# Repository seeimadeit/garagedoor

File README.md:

# Garage Door Opener

Project Status: Unstable - in development

 * circuit design - stable
* iphone software - unstable
* arduino software - unstable
* box housing - stable/regular changes

Project located @ 
[https://github.com/seeimadeit/garagedoor](https://github.com/seeimadeit/garagedoor "Github")
and [https://seeimadeit.wordpress.com/](https://seeimadeit.wordpress.com/ "Wordpress")

This hardware device is a simple Arduino based relay controller, it uses the Adafruit BLE nRF8001 [http://www.adafruit.com/products/1697](http://www.adafruit.com/products/1697 "Adafruit website").

Stuff I use to make it

* Hardware
	1. circuitboard Eagle CAD 7.4.0
	2. Housing Cubify Design 2014
* Software
	1. Apple XCode 7.1.x, Swift 2 - iPhone
	2. Arduino 1.6.5
	3. Libraries
		* MD5 - https://github.com/scottmac/arduino
		* BLE - https://github.com/sandeepmistry/arduino-BLEPeripheral

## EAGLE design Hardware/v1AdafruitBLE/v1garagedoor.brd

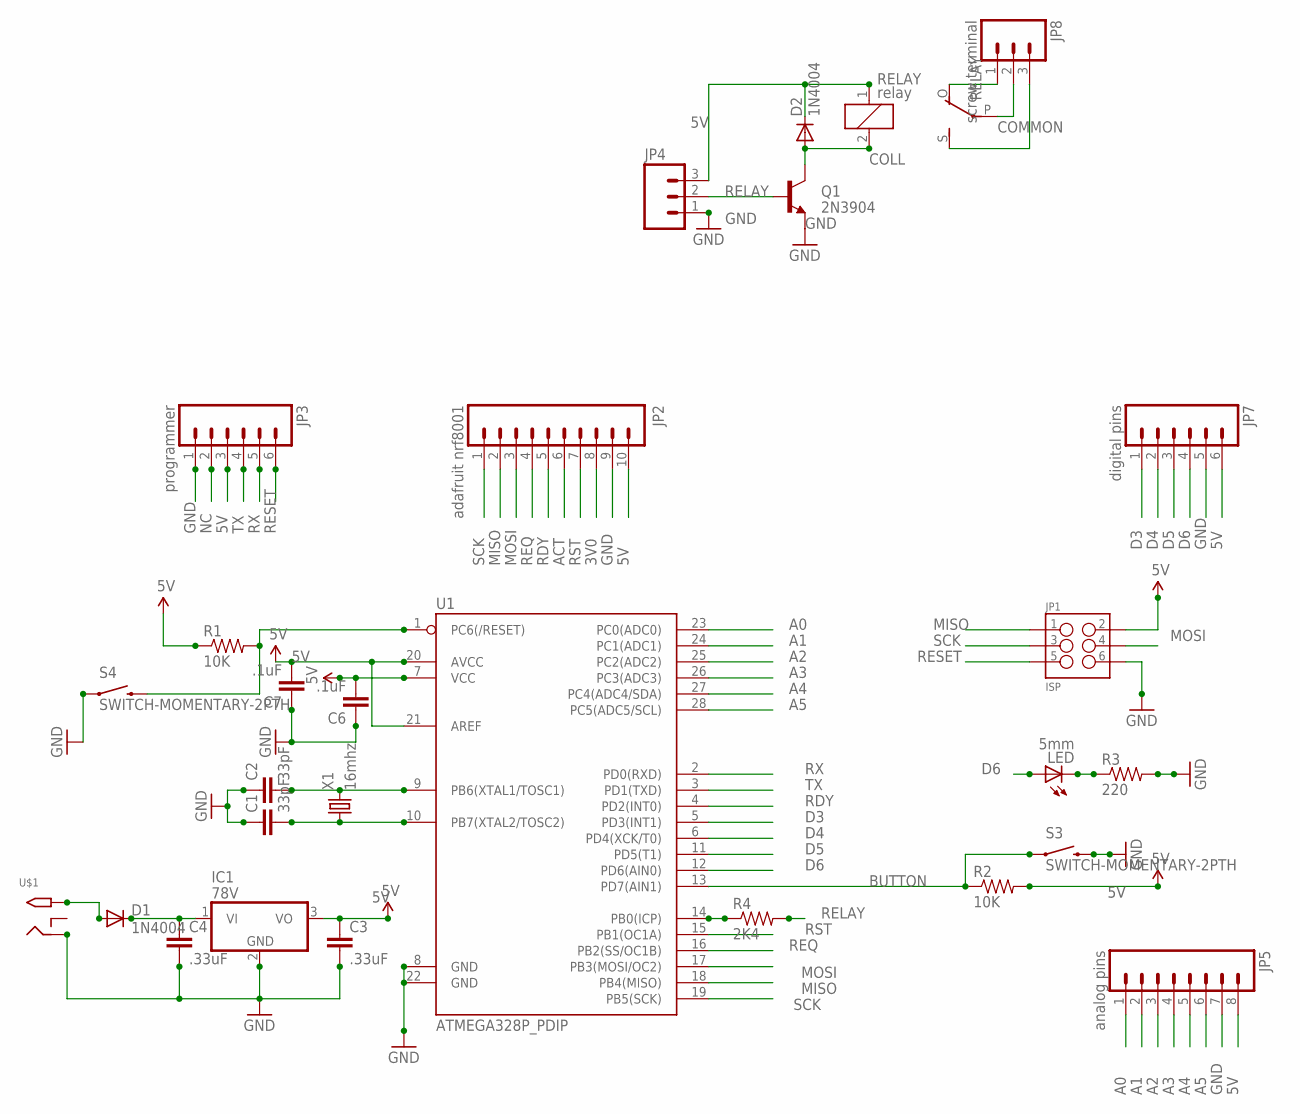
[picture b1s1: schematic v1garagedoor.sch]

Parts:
C1, C2: 33pF; CAP-PTH-5MM; MOUSER 594-S200K25SL0N63L6R
C3, C4: .33uF; CAP-PTH-SMALL-KIT; MOUSER 810-FK18X5R1A334K
C6, C7: .1uF; CAP-PTH-SMALL-KIT; MOUSER 810-FK18X5R1A334K
D1, D2: 1N4004; DO41-10; MOUSER 621-1N4004
IC1: 78V; TO220V; MOUSER 863-MC7805CTG
JP1: ISP; 2X3-NS; MOUSER 571-5-146252-3
JP2: adafruit nrf8001; 1X10; MOUSER 992-10FX1-254MM
JP3: programmer; 1X06_NO_SILK
JP4: M03LOCK; 1X03_LOCK
JP5: analog pins; 1X08
JP7: digital pins; 1X06_NO_SILK
JP8: screw terminal; SCREWTERMINAL-3.5MM-3
LED: 5mm; LED5MM
Q1: 2N3904; TO-92; MOUSER 610-2N3904
R1, R2: 10K; AXIAL-0.3; MOUSER 603-CFR-25JR-5210K
R3: 220; AXIAL-0.3; MOUSER 603-CFR-25JR-52220R
R4: 2K4; AXIAL-0.3; MOUSER 603-CFR-25JR-52-680R
RELAY: relay; ZF112; MOUSER 655-ORWH-SH105D1F000
S3, S4: SWITCH-MOMENTARY-2PTH; TACTILE-PTH; MOUSER 693-1301.9301
U1: ATMEGA328P_PDIP; DIL28-3; MOUSER 556-ATMEGA328P-PU
U$1: 2.1MMJACKTHM; PJ-102A; MOUSER 992-CON-SOCJ-2155
X1: 16mhz; TC38H; MOUSER 520-160-20-46X

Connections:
3V0: JP2.8
5V: C3.1, C6.2, C7.2, D2.C, IC1.3 (VO), JP1.2, JP2.10, JP3.3, JP4.3, JP5.8, JP7.6, R1.P$1 (1), R2.P$2 (2), RELAY.1, U1.7 (VCC), U1.20 (AVCC), U1.21 (AREF)
12V: D1.A, U$1.TIP
A0: JP5.1, U1.23 (PC0(ADC0))
A1: JP5.2, U1.24 (PC1(ADC1))
A2: JP5.3, U1.25 (PC2(ADC2))
A3: JP5.4, U1.26 (PC3(ADC3))
A4: JP5.5, U1.27 (PC4(ADC4/SDA))
A5: JP5.6, U1.28 (PC5(ADC5/SCL))
ACT: JP2.6
BUTTON: R2.P$1 (1), S3.1, U1.13 (PD7(AIN1))
COLL: D2.A, Q1.3 (C), RELAY.2
COMMON: JP8.2, RELAY.P
D3: JP7.1, U1.5 (PD3(INT1))
D4: JP7.2, U1.6 (PD4(XCK/T0))
D5: JP7.3, U1.11 (PD5(T1))
D6: JP7.4, LED.A, U1.12 (PD6(AIN0))
GND: C1.1, C2.1, C3.2, C4.2, C6.1, C7.1, IC1.2 (GND), JP1.6, JP2.9, JP3.1, JP4.1, JP5.7, JP7.5, Q1.1 (E), R3.P$2 (2), S3.3 (2), S4.1, U1.8 (GND), U1.22 (GND), U$1.RING
MISO: JP1.1, JP2.2, U1.18 (PB4(MISO))
MOSI: JP1.4, JP2.3, U1.17 (PB3(MOSI/OC2))
unnamed: C2.2, U1.9 (PB6(XTAL1/TOSC1)), X1.2
unnamed: C1.2, U1.10 (PB7(XTAL2/TOSC2)), X1.1
unnamed: C4.1, D1.C, IC1.1 (VI)
unnamed: LED.K (C), R3.P$1 (1)
unnamed: JP8.1, RELAY.O
unnamed: JP8.3, RELAY.S
unnamed: R4.P$1 (1), U1.14 (PB0(ICP))
NC: JP3.2
RDY: JP2.5, U1.4 (PD2(INT0))
RELAY: JP4.2, Q1.2 (B), R4.P$2 (2)
REQ: JP2.4, U1.16 (PB2(SS/OC1B))
RESET: JP1.5, JP3.6, R1.P$2 (2), S4.3 (2), U1.1 (PC6(/RESET))
RST: JP2.7, U1.15 (PB1(OC1A))
RX: JP3.5, U1.2 (PD0(RXD))
SCK: JP1.3, JP2.1, U1.19 (PB5(SCK))
TX: JP3.4, U1.3 (PD1(TXD))

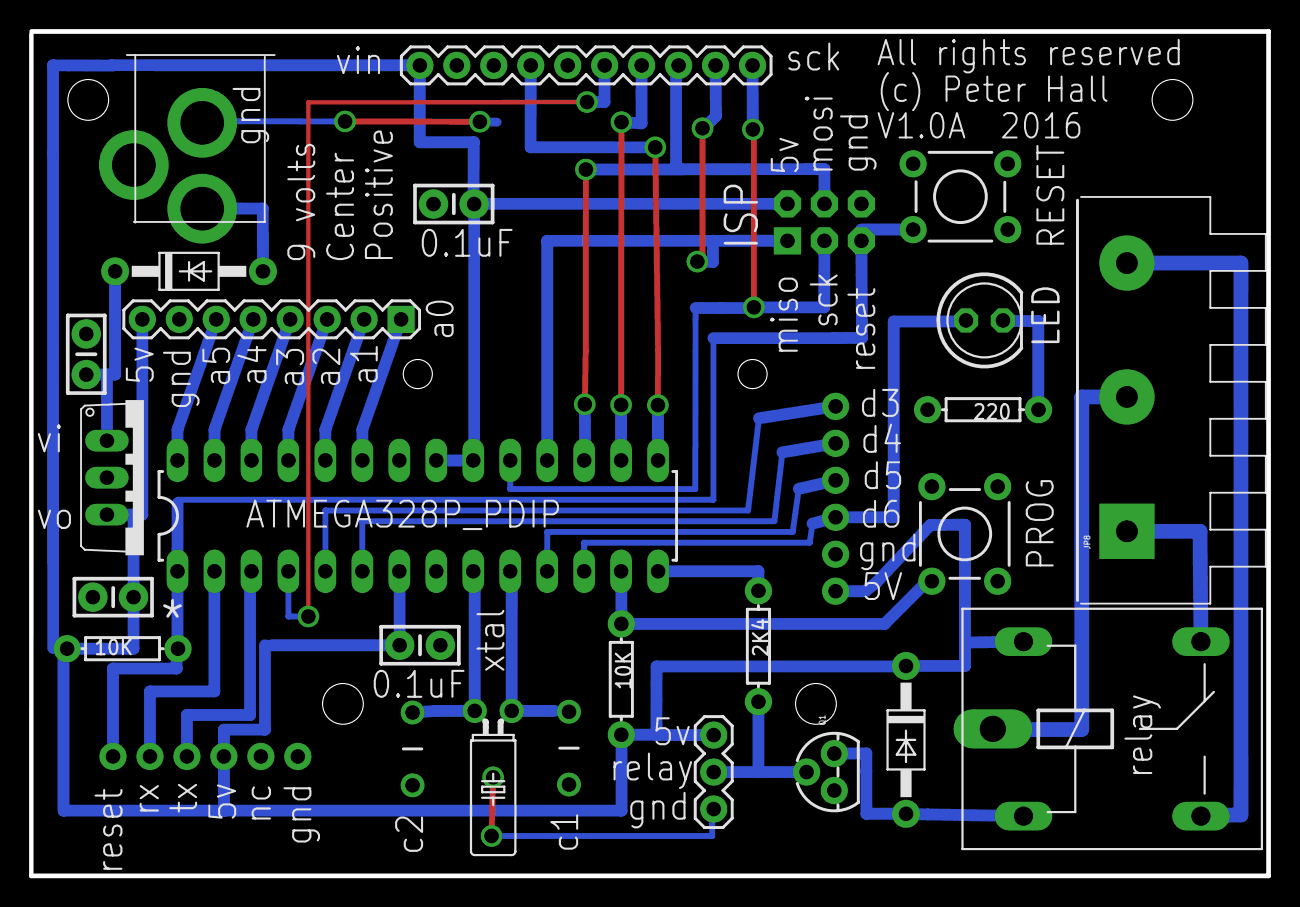
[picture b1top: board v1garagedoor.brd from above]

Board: 2 copper layers, 85.0 x 58.0 mm, 28 parts (0 on the bottom side), 33 nets.

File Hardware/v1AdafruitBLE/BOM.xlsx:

Part | Value | Device | Package | Description | MANF | MOUSER | Required | Optional | unit cost | product cost | DIGIKEY | Unit Cost | product cost
C1/C2 | 33pF | CAPPTH1 | CAP-PTH-5MM | 33pF Capacitor | 1C10C0G330J050B | 75-1C10C0G330J050B | 2 |  | 0.15 | 0.3 | 1265PH-ND | 0.31 | 0.62
C6/C7 | 0.1uF |  |  | 0.1uF Capacitor decoupling | 21RZ310-RC | 21RZ310-RC | 2 |  | 0.08 | 0.16 | 478-5741-ND | 0.24 | 0.48
C3/C4 | .33uF | CAPKIT | CAP-PTH-SMALL-KIT | 0.33uF Capacitor | FK18X7R1E334K | 810-FK18X7R1E334K | 2 |  | 0.31 | 0.62 | 445-5306-ND | 0.32 | 0.64
D1/D2 | 1N4004 | 1N4004 | DO41-10 | DIODE | 1N4004-T | 621-1N4004 | 2 |  | 0.13 | 0.26 | 1N4004DICT-ND | 0.13 | 0.26
IC1 | 7805 | 78V | TO220V | Positive VOLTAGE REGULATOR 5v | NCP7805TG | 863-NCP7805TG | 1 |  | 0.47 | 0.47 | MC7805CTGOS-ND | 0.45 | 0.45
JP1 | ISP | M03X2NO_SILK | 2X3-NS | 2x3 .1 header." | 5-146252-3 | 571-5-146252-3 | 1 |  | 0.42 | 0.42 | 5-146252-3-ND | 0.42 | 0.42
JP2 | adafruit nrf8001 | M10SILK_FEMALE_PTH | 1X10 | Header 10, .1 female | 10Fx1-254mm | 992-10FX1-254MM | 1 |  | 0.7 | 0.7 | SAM1119-10-ND | 1.06 | 1.06
JP3 | programmer | M06NO_SILK_FEMALE_PTH | 1X06_NO_SILK | Header 6 |  |  | 0 | 1 |  | 0 |  |  | 0
JP4 | test point relay | M03LOCK | 1X03_LOCK | Header 3 |  |  | 0 | 1 |  | 0 |  |  | 0
JP5 | analog pins | M08SILK_FEMALE_PTH | 1X08 | Header 8 |  |  | 0 | 1 |  | 0 |  |  | 0
JP7 | digital pins | M06NO_SILK_FEMALE_PTH | 1X06_NO_SILK | Header 6 |  |  | 0 | 1 |  | 0 |  |  | 0
JP8 | screw terminal | M03SCREW | SCREWTERMINAL-3.5MM-3 | Header 3 |  |  | 0 | 1 |  | 0 |  |  | 0
LED | 5mm | LED5MM | LED5MM | LED green 1.8Fv 5mm round bulb | LTL2R3KGD-EM | 859-LTL2R3KGD-EM | 1 |  | 0.08 | 0.08 | 160-1852-ND | 0.3 | 0.3
Q1 | 2N3904 | TRANSISTOR_NPN2N3904 | TO-92 | Generic NPN BJT | 2N3904BU | 512-2N3904BU | 1 |  | 0.19 | 0.19 | 2N3904FS-ND | 0.18 | 0.18
R1/R2 | 10K | RESISTORAXIAL-0.3 | AXIAL-0.3 | 10K Resistor | CFR-25JR-52-10K | 603-CFR-25JR-5210K | 2 |  | 0.1 | 0.2 | 10KQBK-ND | 0.1 | 0.2
R4 | 2.4K | RESISTORAXIAL-0.3 | AXIAL-0.3 | 2K4 Resistor | 291-2.4K-RC | 291-2.4K-RC | 1 |  | 0.1 | 0.1 | CF14JT2K40CT-ND | 0.1 | 0.1
R3 | 220 | RESISTORAXIAL-0.3 | AXIAL-0.3 | 220 Resistor | CFR-25JR-52-220R | 603-CFR-25JR-52220R | 1 |  | 0.1 | 0.1 | CF14JT220RCT-ND | 0.1 | 0.1
RELAY | relay | ZF112 | ZF112 | RELAY | ORWH-SH-105D1F,000 | 655-ORWH-SH105D1F000 | 1 |  | 1.22 | 1.22 | PB2032-ND | 1.46 | 1.46
S3 | SWITCH-MOMENTARY-2PTH | SWITCH-MOMENTARY-2PTH | TACTILE-PTH | Various NO switches- pushbuttons, reed, etc | 1301.9301 | 693-1301.9301 | 2 | 0 | 0.28000000000000003 | 0.56000000000000005 | 1301.9301-ND,486-1943-ND | 0.36 | 0.72
U$1 | 2.1MMJACKTHM | 2.1MMJACKTHM | PJ-102A | 2.1mm x 5.5mm THM DC jack with internal switch. Digikey part #PJ-102A, 4UCON pa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 | CON-SOCJ-2155 | 992-CON-SOCJ-2155 | 1 |  | 1 | 1 | CP-102A-ND | 1 | 1
U1 | ATMEGA328P_PDIP | ATMEGA328P_PDIP | DIL28-3 | uC used in the Arduino | ATMEGA328P-PU | 556-ATMEGA328P-PU | 1 |  | 3.7 | 3.7 | ATMEGA328P-PU-ND | 3.7 | 3.7
X1 | 16mhz | CRYSTALTC38H | TC38H | 16 MHz ECS Crystal 20pF | ECS-160-20-46X | 520-160-20-46X | 1 |  | 0.46 | 0.46 | XC1759-ND | 0.46 | 0.46
 |  |  |  | Bluetooth / 802.15.1 Development Tools Bluetooth Low Energy nRF8001 breakout | 1697 | 485-1697 | 1 |  | 19.95 | 19.95 | 1528-1199-ND | 19.95 | 19.95
 |  |  |  | Barrier Terminal Blocks 3P TRI-BARRIER .375" | 6PCV-03-006 | 571-514376524 | 1 |  | 1.42 | 1.42 | A98482-ND | 1.42 | 1.42
 |  |  |  | IC & Component Sockets SOCKET 28POS .3" IC OPEN FRAME | 4828-3004-CP | 517-4828-3004-CP | 1 |  | 0.77 | 0.77 | 3M5480-ND | 0.77 | 0.77
 |  |  |  | Circuit Board |  | v1garagedoor.brd | 1 |  | 13.22 | 13.22 |  |  | 13.22
 |  |  |  |  |  |  |  |  |  | 45.900000000000006 |  |  | 47.510000000000005
 |  |  |  | OSH Park |  |  |  |  | 39.660000000000004

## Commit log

2015-11-17 initial commit, I hope I have everything
2015-11-18 playing with the housing
2015-11-25 still working on the housing, added some accessibility holes, to access the power screws. resized the mount holes.
2015-11-26 still working on the housing, added a spring to the push button, made some changes to the button design.
2015-12-03 changes to the housing
2015-12-07 some changes to the housing started on the documentation
2015-12-07 updated build instructions table of contents
2015-12-21 added some documentation made some changes to the board layout because of the v1 board has some needed changes. I expect there to be a few more changes, around the silkscreen output
2016-02-15 just updating the repo

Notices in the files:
Hardware/v1AdafruitBLE/v1garagedoor.brd:
All rights reserved
parts and their libraries:
SparkFun-Capacitors: Licensing: Creative Commons ShareAlike 4.0 International - https://creativecommons.org/licenses/by-sa/4.0
